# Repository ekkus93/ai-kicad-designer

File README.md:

# ai-kicad-designer
AI assisted Kicad designer

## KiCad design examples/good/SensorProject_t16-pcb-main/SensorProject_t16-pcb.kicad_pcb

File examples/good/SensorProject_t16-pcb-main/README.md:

# SensorProject_t16-pcb
Connect multiple temperature sensors to an analog digital converter.

##  Status: Working Prototype.

## Summary

Kicad PCB design to connect multiple (up to 16) thermistor temperature sensors to an ads1115 with I2C
output to connect to an MCU. Connectors are  2-pin JST XH_B2B-XH-A, as commonly used on NTC 10K 3950 sensors.
These sensors are inexpensive and easily available in lengths up to 3m. 
Measurements are broadcast with LoRa.

Software for this hardware is in repository https://github.com/pdgilbert/SensorProject_t16.
The overall project, recording station, etc., 
is described in repository https://github.com/pdgilbert/SensorProject.

The `.png` and `jpg` files are produced from kicad in the `3D Viewer`  with `File > Export Current View as ...`.

See also file ProjectNotes.txt for additional hardware details.

## History

To see tags and tag messages use  git tag -n 

 - Version 0.2.2 2025-09 includes an stm32f411 MCU. It has an unshielded LoRa module RFM95W.
   It works with no necessary hardware adjustments. Two minor fixes to the BOM are added.
   (The HSE, LSE and RTC are still untested.)

 - Version 0.2.0 2025-05 includes an stm32f411 MCU. It has an unshielded LoRa module RFM95W.
   It needs some hardware re-adjustment to work.

 - Version 0.1.1 2025-01 has pull up resistors added but has not been manufactured/tested.

 - Version 0.1.0 2024-05 needs manual addition of pull up resistors on the I2C lines. 
   With this modification it works with `blackpill` `stm32f401` or `stm32f411` inserted.
   This versin has no LoRa module.

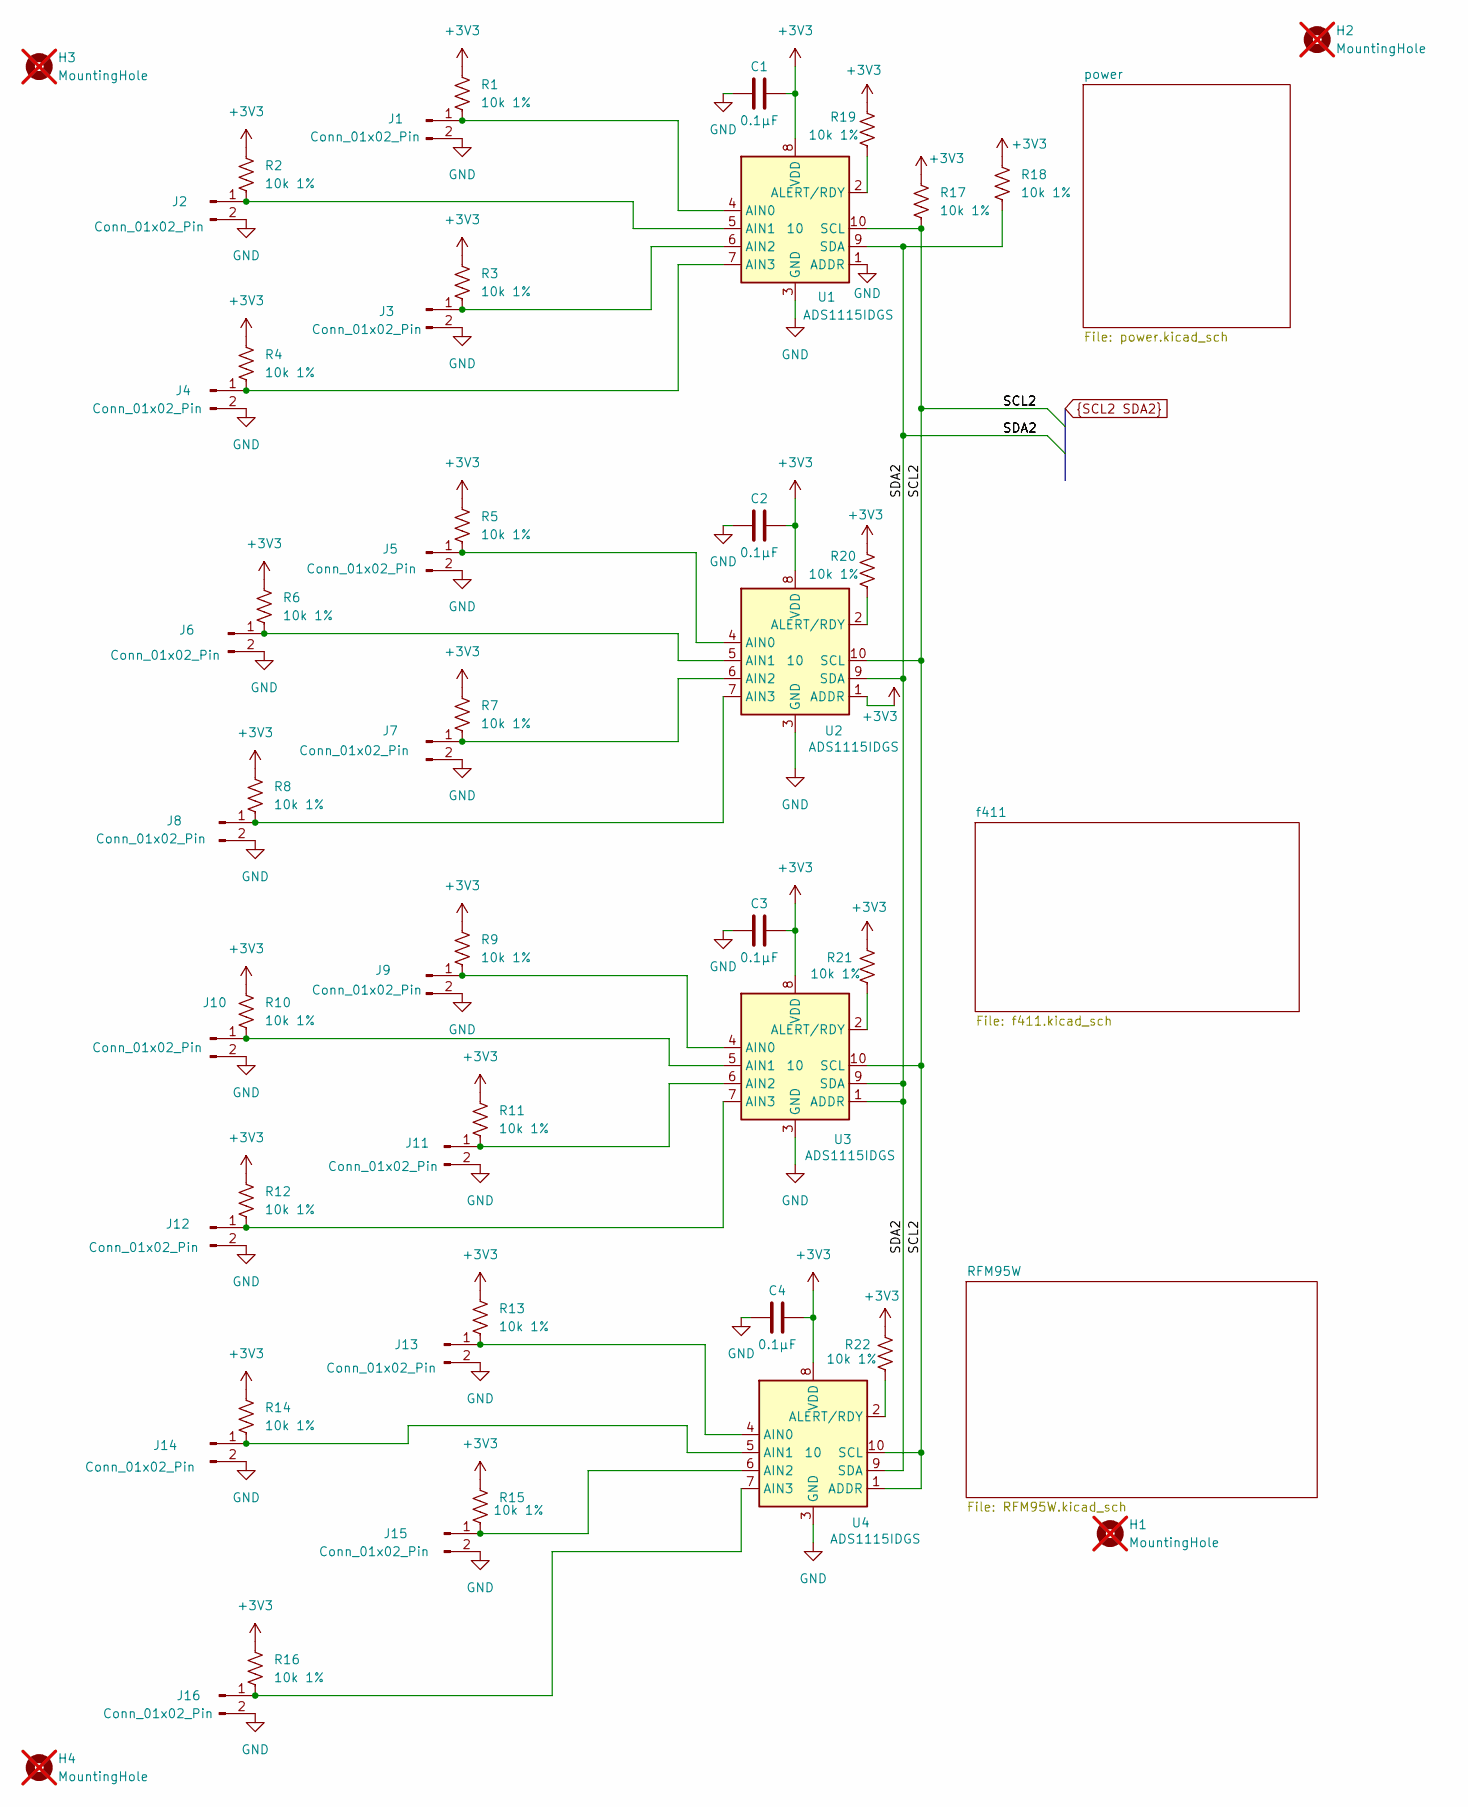
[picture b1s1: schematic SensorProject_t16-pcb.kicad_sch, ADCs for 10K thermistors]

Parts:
C1, C2, C3, C4: 0.1µF; C_0402_1005Metric
H1, H2, H3, H4: MountingHole; MountingHole_2.2mm_M2_ISO7380_Pad; not fitted
J1, J2, J3, J4, J5, J6, J7, J8, J9, J10, J11, J12, J13, J14, J15, J16: Conn_01x02_Pin; JST_XH_B2B-XH-A_1x02_P2.50mm_Vertical; MfgPart B2B-XH-A
R1, R2, R3, R4, R5, R6, R7, R8, R9, R10, R11, R12, R13, R14, R15, R16, R17, R18, R19, R20, R21, R22: 10k 1%; R_0402_1005Metric
U1, U2, U3, U4: ADS1115IDGS; TSSOP-10_3x3mm_P0.5mm; MfgPart ADS1115IDGS

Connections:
+3V3: C1.1, C2.1, C3.1, C4.1, R1.1, R2.1, R3.1, R4.1, R5.1, R6.1, R7.1, R8.1, R9.1, R10.1, R11.1, R12.1, R13.1, R14.1, R15.1, R16.1, R17.1, R18.1, R19.1, R20.1, R21.1, R22.1, U1.8 (VDD), U2.1 (ADDR), U2.8 (VDD), U3.8 (VDD), U4.8 (VDD); also elsewhere on the board
GND: C1.2, C2.2, C3.2, C4.2, J1.2, J2.2, J3.2, J4.2, J5.2, J6.2, J7.2, J8.2, J9.2, J10.2, J11.2, J12.2, J13.2, J14.2, J15.2, J16.2, U1.1 (ADDR), U1.3 (GND), U2.3 (GND), U3.3 (GND), U4.3 (GND); also elsewhere on the board
unnamed: J1.1, R1.2, U1.4 (AIN0)
unnamed: J2.1, R2.2, U1.5 (AIN1)
unnamed: J3.1, R3.2, U1.6 (AIN2)
unnamed: J4.1, R4.2, U1.7 (AIN3)
unnamed: J5.1, R5.2, U2.4 (AIN0)
unnamed: J6.1, R6.2, U2.5 (AIN1)
unnamed: J7.1, R7.2, U2.6 (AIN2)
unnamed: J8.1, R8.2, U2.7 (AIN3)
unnamed: J9.1, R9.2, U3.4 (AIN0)
unnamed: J10.1, R10.2, U3.5 (AIN1)
unnamed: J11.1, R11.2, U3.6 (AIN2)
unnamed: J12.1, R12.2, U3.7 (AIN3)
unnamed: J13.1, R13.2, U4.4 (AIN0)
unnamed: J14.1, R14.2, U4.5 (AIN1)
unnamed: J15.1, R15.2, U4.6 (AIN2)
unnamed: J16.1, R16.2, U4.7 (AIN3)
unnamed: R19.2, U1.2 (ALERT/RDY)
unnamed: R20.2, U2.2 (ALERT/RDY)
unnamed: R21.2, U3.2 (ALERT/RDY)
unnamed: R22.2, U4.2 (ALERT/RDY)
SCL2: R17.2, U1.10 (SCL), U2.10 (SCL), U3.10 (SCL), U4.1 (ADDR), U4.10 (SCL); also elsewhere on the board
SDA2: R18.2, U1.9 (SDA), U2.9 (SDA), U3.1 (ADDR), U3.9 (SDA), U4.9 (SDA); also elsewhere on the board

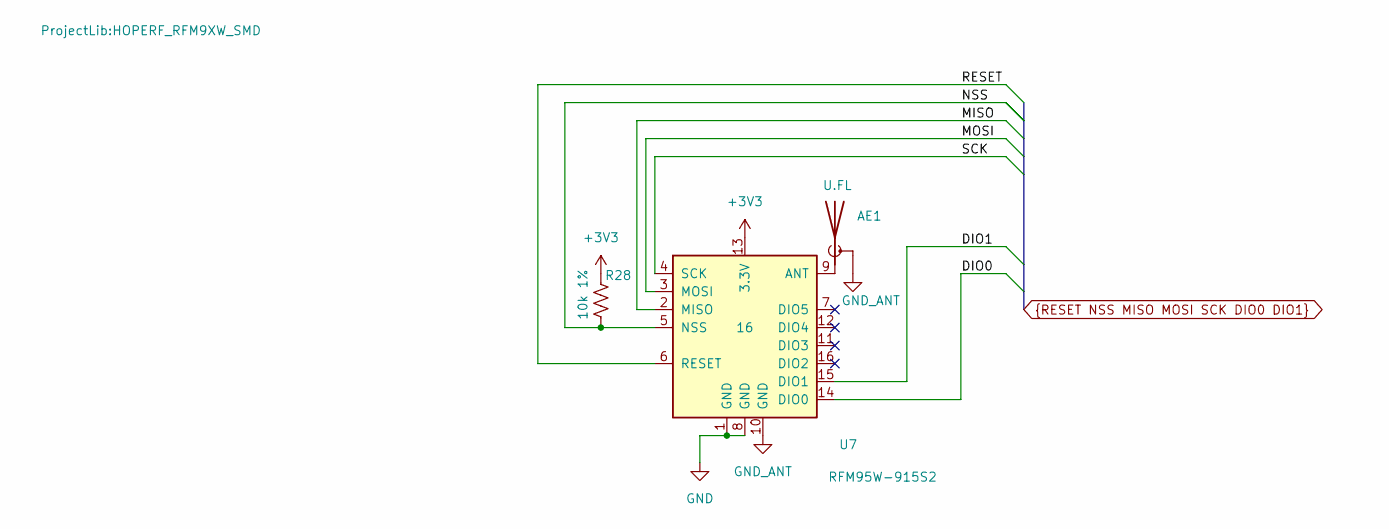
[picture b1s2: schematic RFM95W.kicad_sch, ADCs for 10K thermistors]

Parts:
AE1: U.FL; U.FL_Molex_MCRF_73412-0110_Vertical; MfgPart U.FL-R-SMT-K(800)
R28: 10k 1%; R_0402_1005Metric
U7: RFM95W-915S2; HOPERF_RFM9XW_SMD; MfgPart RFM95W-915S2

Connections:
+3V3: R28.1, U7.13 (3.3V); also elsewhere on the board
DIO0: U7.14 (DIO0); also elsewhere on the board
DIO1: U7.15 (DIO1); also elsewhere on the board
GND: U7.1 (GND), U7.8 (GND); also elsewhere on the board
GND_ANT: AE1.2 (Shield), U7.10 (GND)
MISO: U7.2 (MISO); also elsewhere on the board
MOSI: U7.3 (MOSI); also elsewhere on the board
NSS: R28.2, U7.5 (NSS); also elsewhere on the board
unnamed: AE1.1 (A), U7.9 (ANT)
RESET: U7.6 (RESET); also elsewhere on the board
SCK: U7.4 (SCK); also elsewhere on the board

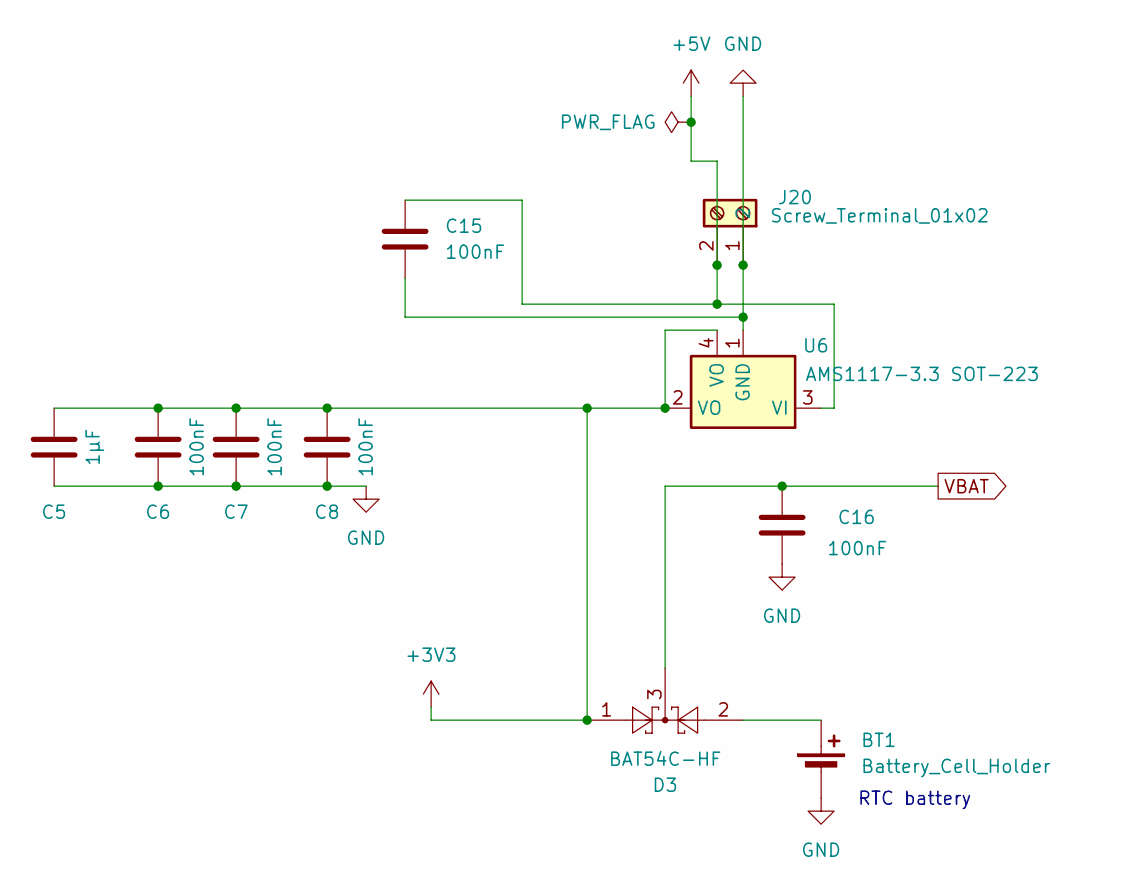
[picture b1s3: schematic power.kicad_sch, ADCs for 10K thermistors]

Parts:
BT1: Battery_Cell_Holder; BatteryHolder_LINX_BAT-HLD-012-SMT; MfgPart BAT-HLD-012-SMT
C5: 1µF; C_0402_1005Metric
C6, C7, C8, C15, C16: 100nF; C_0402_1005Metric
D3: BAT54C-HF; SOT-23; MfgPart BAT54C-HF
J20: Screw_Terminal_01x02; TerminalBlock_Phoenix_MPT-0,5-2-2.54_1x02_P2.54mm_Horizontal; MfgPart KF128-2.54-2P
U6: AMS1117-3.3 SOT-223; SOT-223; MfgPart AMS1117-3.3

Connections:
+3V3: C5.1, C6.1, C7.1, C8.1, D3.1, U6.2 (VO), U6.4 (VO); also elsewhere on the board
+5V: C15.1, J20.2, U6.3 (VI)
GND: BT1.2 (-), C5.2, C6.2, C7.2, C8.2, C15.2, C16.2, J20.1, U6.1 (GND); also elsewhere on the board
unnamed: BT1.1 (+), D3.2
VBAT: C16.1, D3.3; also elsewhere on the board

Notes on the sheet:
RTC battery

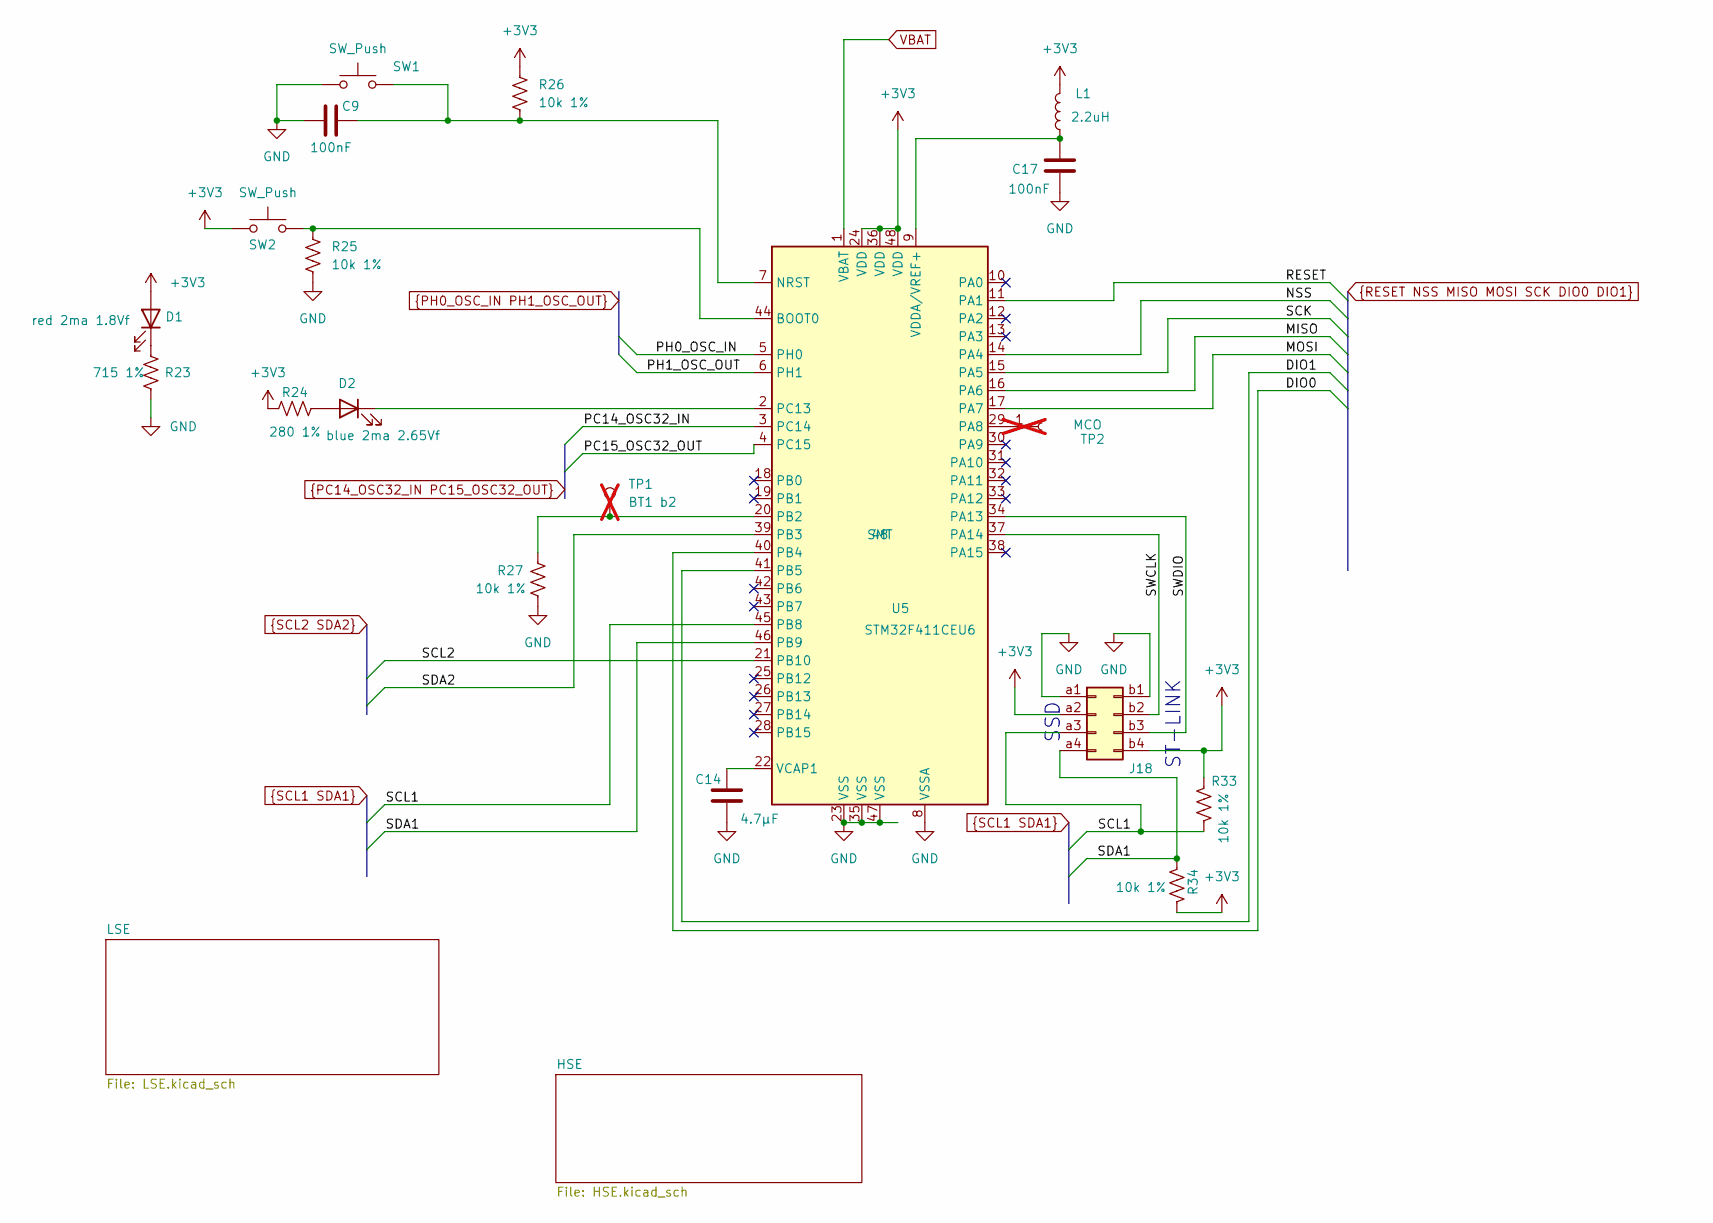
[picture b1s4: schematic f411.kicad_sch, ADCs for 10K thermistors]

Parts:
C9, C17: 100nF; C_0402_1005Metric
C14: 4.7µF; C_0402_1005Metric
D1: red 2ma 1.8Vf; LED_0603_1608Metric; MfgPart APT1608LSECK/J3-PRV
D2: blue 2ma 2.65Vf; LED_0603_1608Metric; MfgPart APT1608LVBC/D
J18: Conn_02x04_Top_Bottom; PinSocket_2x04_P2.54mm_Vertical_SMD; MfgPart HC-PM254-5.0H-2x4PS-02A
L1: 2.2uH; L_0402_1005Metric; MfgPart MLZ1005M2R2WT000
R23: 715 1%; R_0402_1005Metric
R24: 280 1%; R_0402_1005Metric
R25, R26, R27, R33, R34: 10k 1%; R_0402_1005Metric
SW1, SW2: SW_Push; SW_SPST_B3U-1000P; MfgPart B3U-1000P
TP1: BT1 b2; TestPoint_Pad_D1.0mm; not fitted
TP2: MCO; TestPoint_Pad_D1.0mm; not fitted
U5: STM32F411CEU6; QFN-48-1EP_7x7mm_P0.5mm_EP5.6x5.6mm; MfgPart STM32F411CEU6

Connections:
+3V3: D1.2 (A), J18.a2, J18.b4, L1.2, R24.1, R26.1, R33.1, R34.2, SW2.1, U5.24 (VDD), U5.36 (VDD), U5.48 (VDD); also elsewhere on the board
/f411/SWCLK: J18.b2, U5.37 (PA14)
/f411/SWDIO: J18.b3, U5.34 (PA13)
DIO0: U5.40 (PB4); also elsewhere on the board
DIO1: U5.41 (PB5); also elsewhere on the board
GND: C9.1, C14.2, C17.2, J18.a1, J18.b1, R23.2, R25.2, R27.2, SW1.1, U5.8 (VSSA), U5.23 (VSS), U5.35 (VSS), U5.47 (VSS), U5.49 (VSS); also elsewhere on the board
MISO: U5.16 (PA6); also elsewhere on the board
MOSI: U5.17 (PA7); also elsewhere on the board
NSS: U5.14 (PA4); also elsewhere on the board
unnamed: D1.1 (K), R23.1
unnamed: D2.2 (A), R24.2
unnamed: D2.1 (K), U5.2 (PC13)
unnamed: TP2.1, U5.29 (PA8)
unnamed: R25.1, SW2.2, U5.44 (BOOT0)
unnamed: C9.2, R26.2, SW1.2, U5.7 (NRST)
unnamed: R27.1, TP1.1, U5.20 (PB2)
unnamed: C14.1, U5.22 (VCAP1)
unnamed: C17.1, L1.1, U5.9 (VDDA/VREF+)
PC14_OSC32_IN: U5.3 (PC14); also elsewhere on the board
PC15_OSC32_OUT: U5.4 (PC15); also elsewhere on the board
PH0_OSC_IN: U5.5 (PH0); also elsewhere on the board
PH1_OSC_OUT: U5.6 (PH1); also elsewhere on the board
RESET: U5.11 (PA1); also elsewhere on the board
SCK: U5.15 (PA5); also elsewhere on the board
SCL1: J18.a3, R33.2, U5.45 (PB8)
SCL2: U5.21 (PB10); also elsewhere on the board
SDA1: J18.a4, R34.1, U5.46 (PB9)
SDA2: U5.39 (PB3); also elsewhere on the board
VBAT: U5.1 (VBAT); also elsewhere on the board

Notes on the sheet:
SSD
ST-LINK

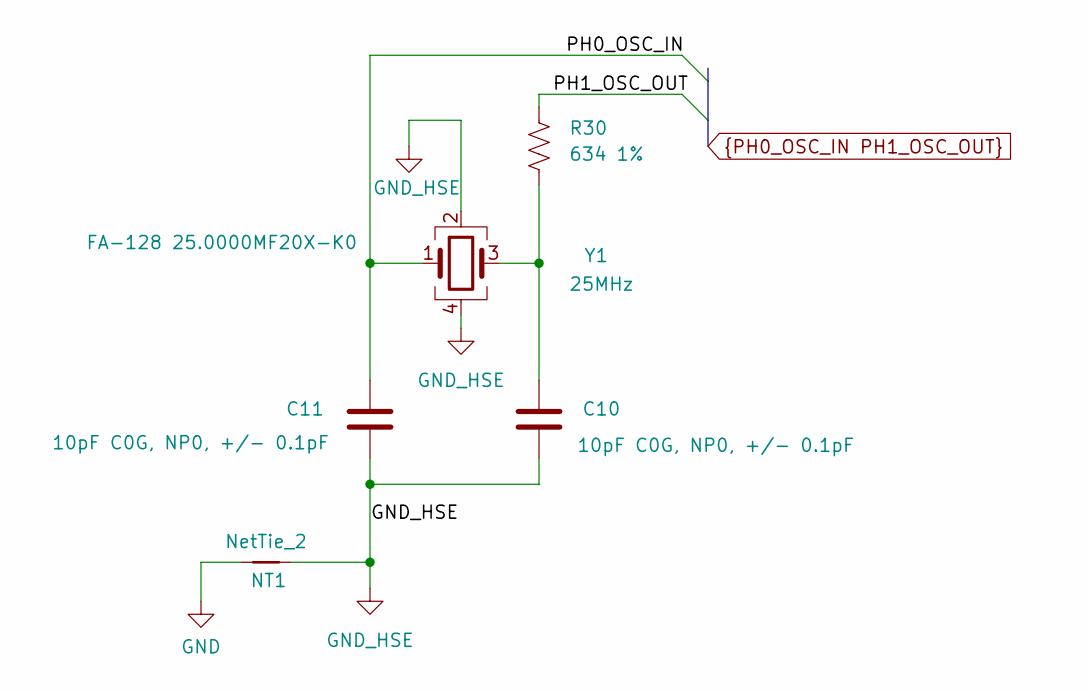
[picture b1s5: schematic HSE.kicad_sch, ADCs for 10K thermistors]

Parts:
C10, C11: 10pF C0G, NP0, +/- 0.1pF; C_0402_1005Metric
NT1: NetTie_2; NetTie-2_SMD_Pad0.5mm
R30: 634 1%; R_0402_1005Metric
Y1: 25MHz; Crystal_SMD_2016-4Pin_2.0x1.6mm; MfgPart FA-128 25.0000MF20X-K0

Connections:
GND: NT1.1; also elsewhere on the board
GND_HSE: C10.1, C11.1, NT1.2, Y1.2, Y1.4
unnamed: C10.2, R30.2, Y1.3
PH0_OSC_IN: C11.2, Y1.1; also elsewhere on the board
PH1_OSC_OUT: R30.1; also elsewhere on the board

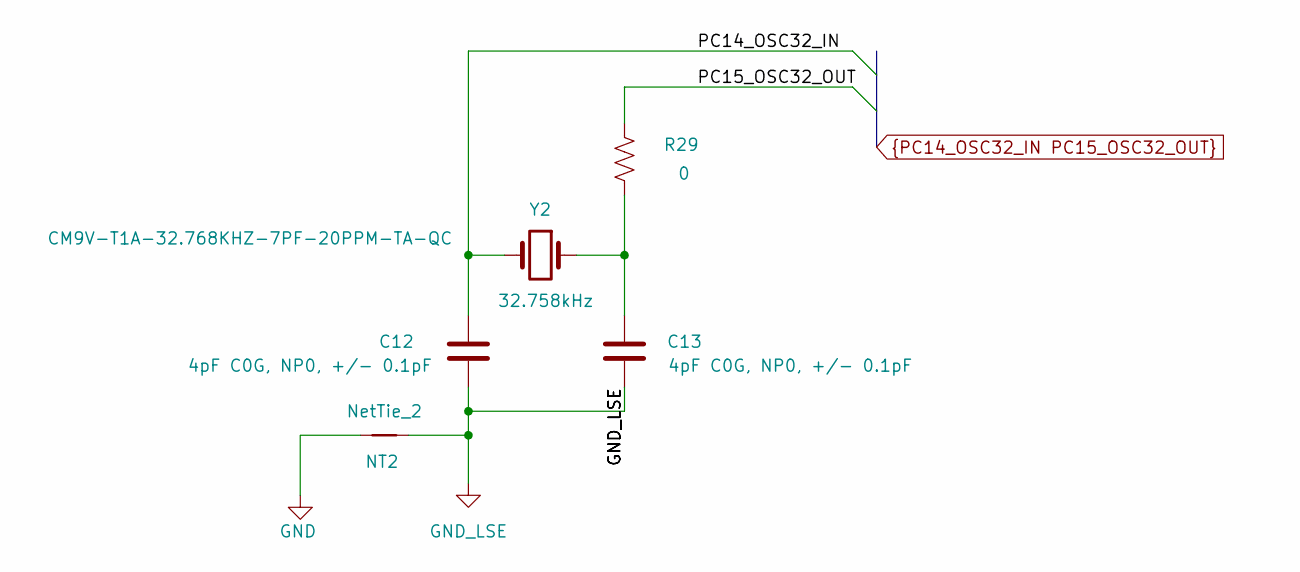
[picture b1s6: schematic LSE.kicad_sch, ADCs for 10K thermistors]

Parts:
C12, C13: 4pF C0G, NP0, +/- 0.1pF; C_0402_1005Metric
NT2: NetTie_2; NetTie-2_SMD_Pad0.5mm
R29: 0; R_0402_1005Metric
Y2: 32.758kHz; Crystal_SMD_MicroCrystal_CM9V-T1A-2Pin_1.6x1.0mm; MfgPart CM9V-T1A-32.768KHZ-7PF-20PPM-TA-QC

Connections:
GND: NT2.1; also elsewhere on the board
GND_LSE: C12.1, C13.1, NT2.2
unnamed: C13.2, R29.2, Y2.1
PC14_OSC32_IN: C12.2, Y2.2; also elsewhere on the board
PC15_OSC32_OUT: R29.1; also elsewhere on the board

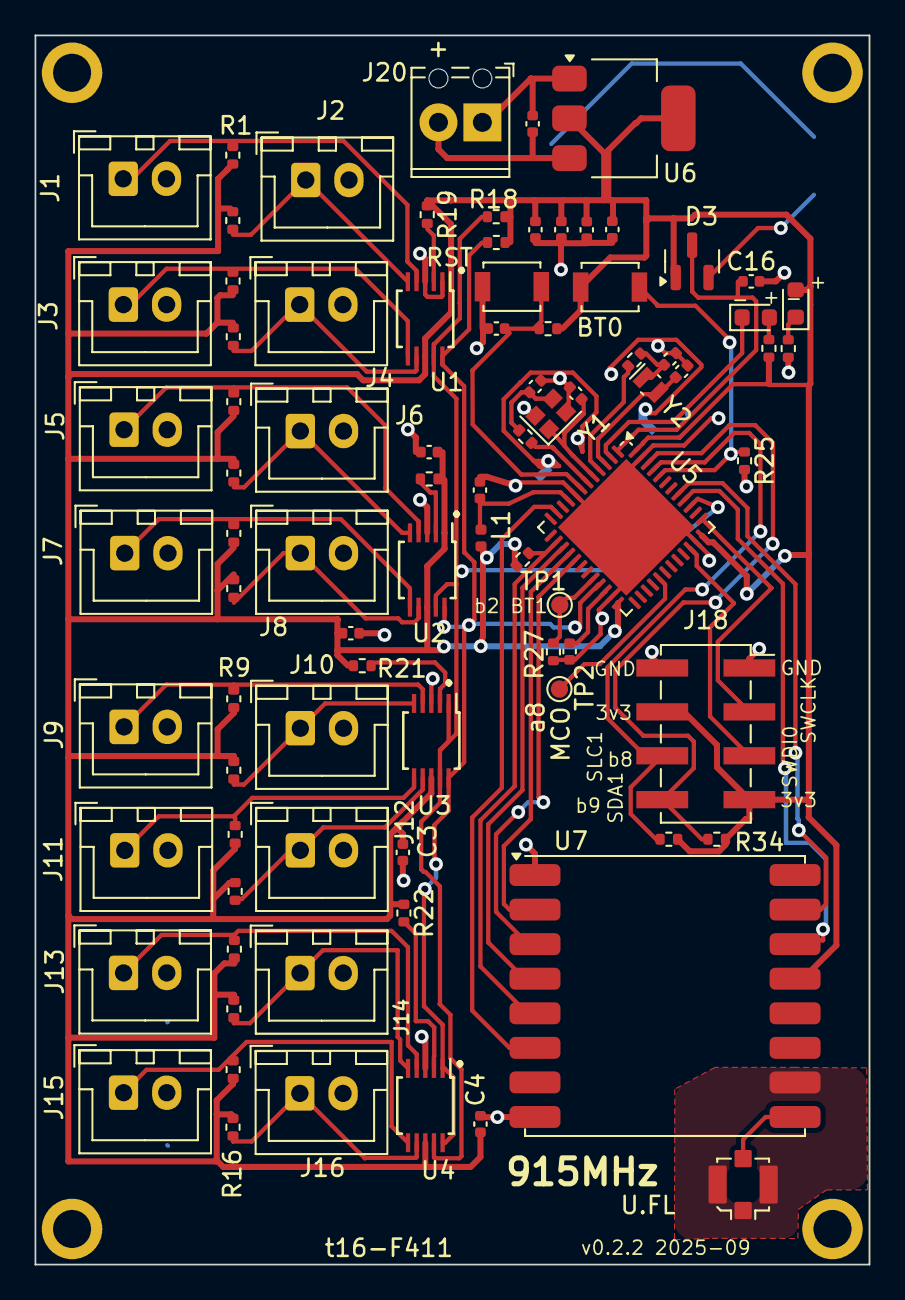
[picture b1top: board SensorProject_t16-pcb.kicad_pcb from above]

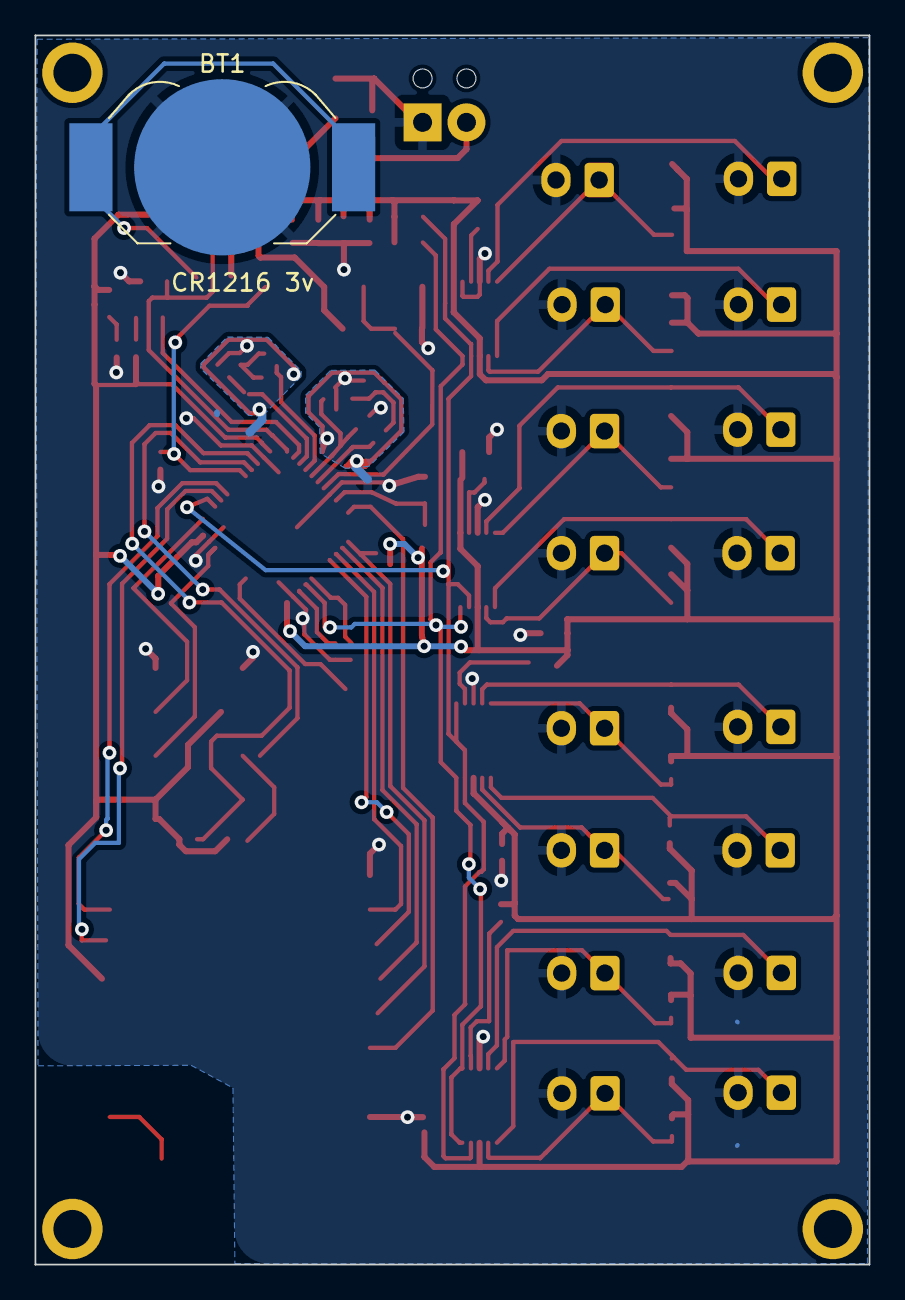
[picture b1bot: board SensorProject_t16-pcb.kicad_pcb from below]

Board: 2 copper layers, 48.3 x 71.1 mm, 92 parts (3 on the bottom side), 57 nets.

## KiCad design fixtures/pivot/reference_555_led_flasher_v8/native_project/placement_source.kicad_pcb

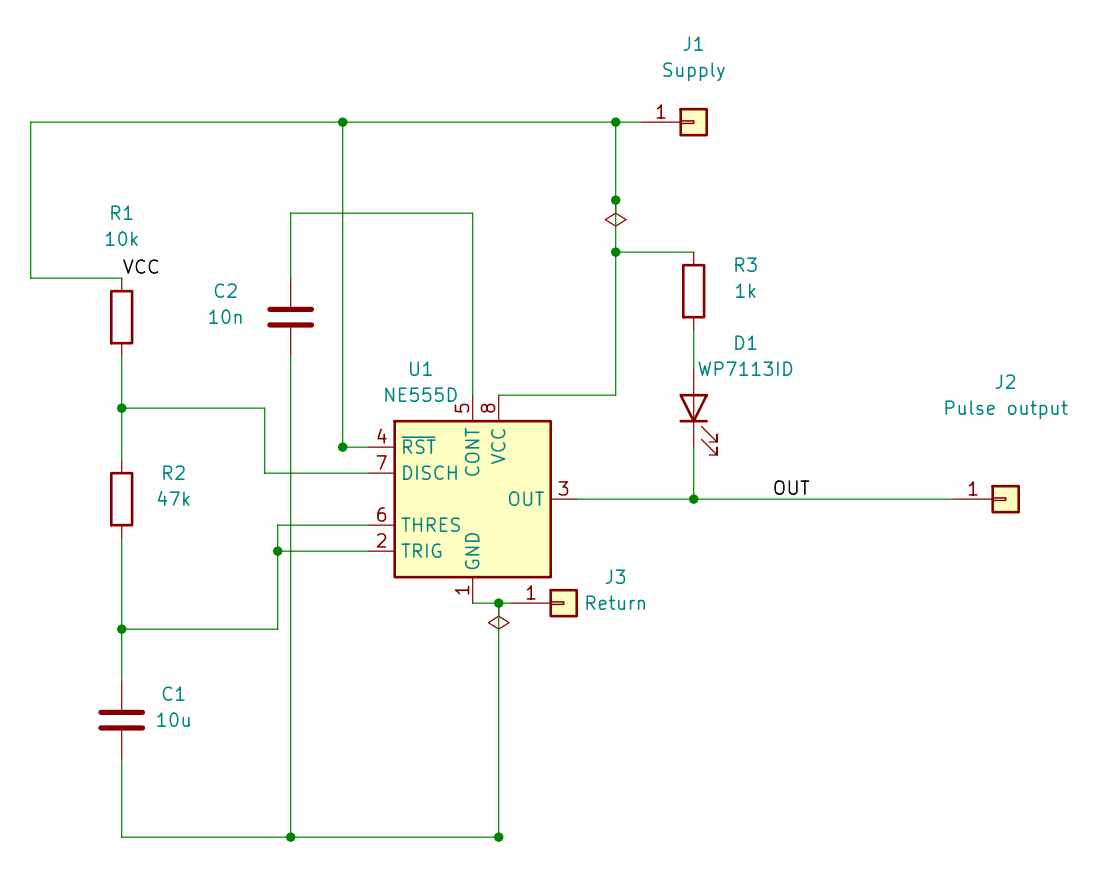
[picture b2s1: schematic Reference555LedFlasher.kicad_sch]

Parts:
C1: 10u
C2: 10n
D1: WP7113ID
J1: Supply
J2: Pulse output
J3: Return
R1: 10k
R2: 47k
R3: 1k
U1: NE555D

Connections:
/OUT: D1.1 (K), J2.1, U1.3 (OUT)
/REF: C1.2, C2.2, J3.1, U1.1 (GND)
/VCC: J1.1, R1.1, R3.1, U1.4 (~RST), U1.8 (VCC)
unnamed: D1.2 (A), R3.2
unnamed: C2.1, U1.5 (CONT)
unnamed: R1.2, R2.1, U1.7 (DISCH)
unnamed: C1.1, R2.2, U1.2 (TRIG), U1.6 (THRES)

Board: 2 copper layers, 10 parts (0 on the bottom side), 7 nets, no tracks yet.
